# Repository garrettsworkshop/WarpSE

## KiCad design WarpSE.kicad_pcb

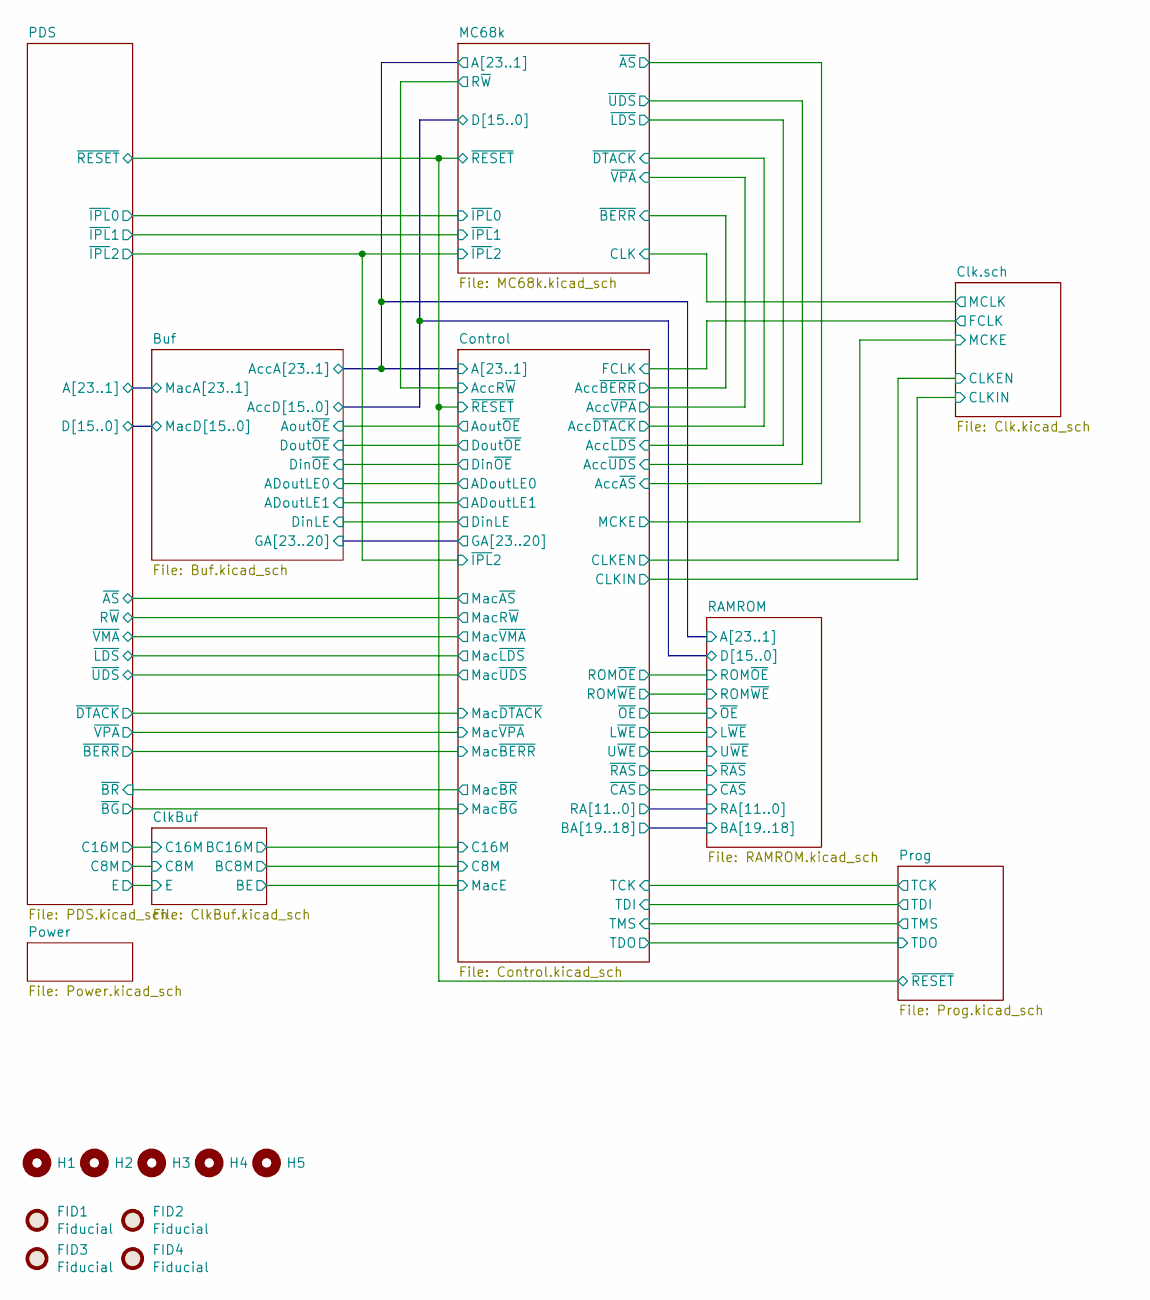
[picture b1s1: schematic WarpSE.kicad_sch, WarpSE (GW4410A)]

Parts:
FID1, FID2, FID3, FID4: Fiducial
H1, H2, H3, H4, H5: PasteHole_1.152mm_NPTH

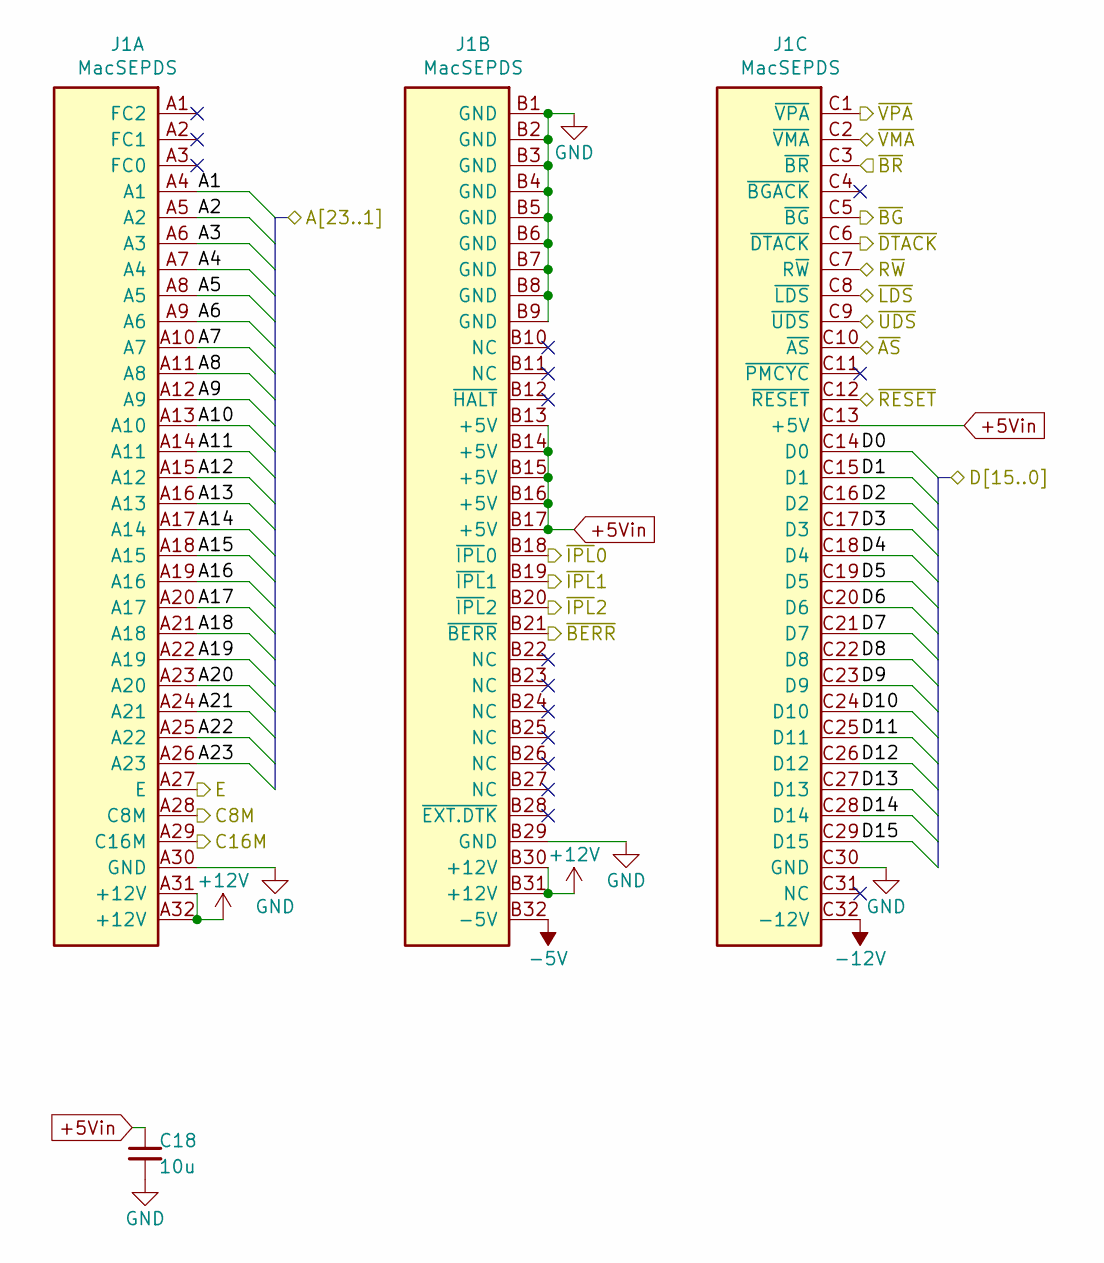
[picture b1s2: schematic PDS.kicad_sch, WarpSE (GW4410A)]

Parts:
C18: 10u; C_0805; LCSC Part C15850
J1: MacSEPDS; DIN41612_R_3x32_Male_Vertical_THT

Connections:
+5Vin: C18.1, J1.B13 (+5V), J1.B14 (+5V), J1.B15 (+5V), J1.B16 (+5V), J1.B17 (+5V), J1.C13 (+5V); also elsewhere on the board
+12V: J1.A31 (+12V), J1.A32 (+12V), J1.B30 (+12V), J1.B31 (+12V)
-5V: J1.B32 (-5V)
-12V: J1.C32 (-12V)
/Buf/MacA1: J1.A4 (A1); also elsewhere on the board
/Buf/MacA2: J1.A5 (A2); also elsewhere on the board
/Buf/MacA3: J1.A6 (A3); also elsewhere on the board
/Buf/MacA4: J1.A7 (A4); also elsewhere on the board
/Buf/MacA5: J1.A8 (A5); also elsewhere on the board
/Buf/MacA6: J1.A9 (A6); also elsewhere on the board
/Buf/MacA7: J1.A10 (A7); also elsewhere on the board
/Buf/MacA8: J1.A11 (A8); also elsewhere on the board
/Buf/MacA9: J1.A12 (A9); also elsewhere on the board
/Buf/MacA10: J1.A13 (A10); also elsewhere on the board
/Buf/MacA11: J1.A14 (A11); also elsewhere on the board
/Buf/MacA12: J1.A15 (A12); also elsewhere on the board
/Buf/MacA13: J1.A16 (A13); also elsewhere on the board
/Buf/MacA14: J1.A17 (A14); also elsewhere on the board
/Buf/MacA15: J1.A18 (A15); also elsewhere on the board
/Buf/MacA16: J1.A19 (A16); also elsewhere on the board
/Buf/MacA17: J1.A20 (A17); also elsewhere on the board
/Buf/MacA18: J1.A21 (A18); also elsewhere on the board
/Buf/MacA19: J1.A22 (A19); also elsewhere on the board
/Buf/MacA20: J1.A23 (A20); also elsewhere on the board
/Buf/MacA21: J1.A24 (A21); also elsewhere on the board
/Buf/MacA22: J1.A25 (A22); also elsewhere on the board
/Buf/MacA23: J1.A26 (A23); also elsewhere on the board
/Buf/MacD0: J1.C14 (D0); also elsewhere on the board
/Buf/MacD1: J1.C15 (D1); also elsewhere on the board
/Buf/MacD2: J1.C16 (D2); also elsewhere on the board
/Buf/MacD3: J1.C17 (D3); also elsewhere on the board
/Buf/MacD4: J1.C18 (D4); also elsewhere on the board
/Buf/MacD5: J1.C19 (D5); also elsewhere on the board
/Buf/MacD6: J1.C20 (D6); also elsewhere on the board
/Buf/MacD7: J1.C21 (D7); also elsewhere on the board
/Buf/MacD8: J1.C22 (D8); also elsewhere on the board
/Buf/MacD9: J1.C23 (D9); also elsewhere on the board
/Buf/MacD10: J1.C24 (D10); also elsewhere on the board
/Buf/MacD11: J1.C25 (D11); also elsewhere on the board
/Buf/MacD12: J1.C26 (D12); also elsewhere on the board
/Buf/MacD13: J1.C27 (D13); also elsewhere on the board
/Buf/MacD14: J1.C28 (D14); also elsewhere on the board
/Buf/MacD15: J1.C29 (D15); also elsewhere on the board
/ClkBuf/C8M: J1.A28 (C8M); also elsewhere on the board
/ClkBuf/C16M: J1.A29 (C16M); also elsewhere on the board
/ClkBuf/E: J1.A27 (E); also elsewhere on the board
/Control/MacR~W: J1.C7 (R~W); also elsewhere on the board
/Control/Mac~AS: J1.C10 (~AS); also elsewhere on the board
/Control/Mac~BERR: J1.B21 (~BERR); also elsewhere on the board
/Control/Mac~BR: J1.C3 (~BR); also elsewhere on the board
/Control/Mac~DTACK: J1.C6 (~DTACK); also elsewhere on the board
/Control/Mac~LDS: J1.C8 (~LDS); also elsewhere on the board
/Control/Mac~UDS: J1.C9 (~UDS); also elsewhere on the board
/Control/Mac~VMA: J1.C2 (~VMA); also elsewhere on the board
/Control/Mac~VPA: J1.C1 (~VPA); also elsewhere on the board
/Control/~IPL2: J1.B20 (~IPL2); also elsewhere on the board
/Control/~RESET: J1.C12 (~RESET); also elsewhere on the board
/MC68k/~IPL0: J1.B18 (~IPL0); also elsewhere on the board
/MC68k/~IPL1: J1.B19 (~IPL1); also elsewhere on the board
/PDS/~BG: J1.C5 (~BG)
GND: C18.2, J1.A30 (GND), J1.B1 (GND), J1.B2 (GND), J1.B3 (GND), J1.B4 (GND), J1.B5 (GND), J1.B6 (GND), J1.B7 (GND), J1.B8 (GND), J1.B9 (GND), J1.B29 (GND), J1.C30 (GND); also elsewhere on the board

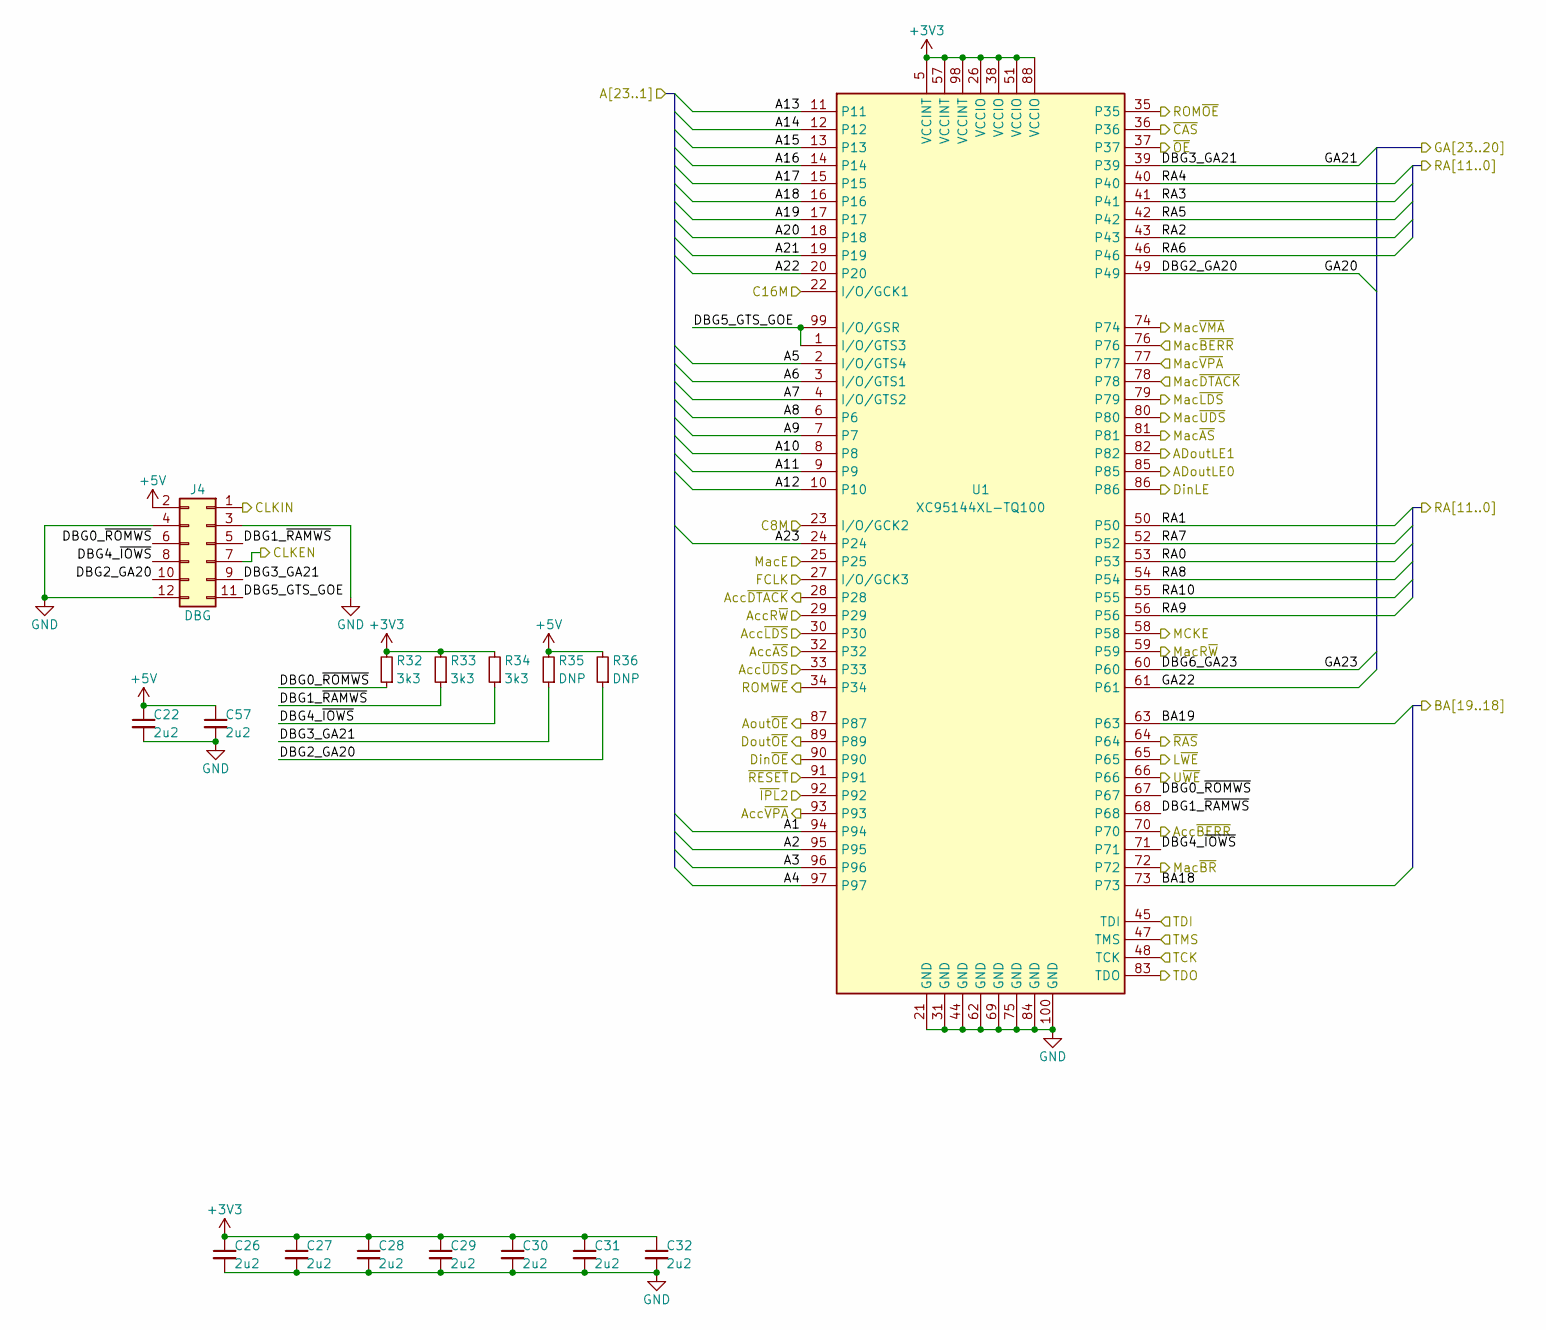
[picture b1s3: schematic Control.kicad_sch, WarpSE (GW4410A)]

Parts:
C22, C26, C27, C28, C29, C30, C31, C32, C57: 2u2; C_0603; LCSC Part C23630
J4: DBG; PinSocket_2x06_P2.00mm_Vertical
R32, R33, R34: 3k3; R_0603; LCSC Part C21190
R35, R36: DNP; R_0603
U1: XC95144XL-TQ100; TQFP-100_14x14mm_P0.5mm; LCSC Part C45126

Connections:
+3V3: C26.1, C27.1, C28.1, C29.1, C30.1, C31.1, C32.1, R32.2, R33.2, R34.2, U1.5 (VCCINT), U1.26 (VCCIO), U1.38 (VCCIO), U1.51 (VCCIO), U1.57 (VCCINT), U1.88 (VCCIO), U1.98 (VCCINT); also elsewhere on the board
+5V: C22.1, C57.1, J4.2, R35.2, R36.2; also elsewhere on the board
/Buf/ADoutLE0: U1.85; also elsewhere on the board
/Buf/ADoutLE1: U1.82; also elsewhere on the board
/Buf/AccA1: U1.94; also elsewhere on the board
/Buf/AccA2: U1.95; also elsewhere on the board
/Buf/AccA3: U1.96; also elsewhere on the board
/Buf/AccA4: U1.97; also elsewhere on the board
/Buf/AccA5: U1.2 (I/O/GTS4); also elsewhere on the board
/Buf/AccA6: U1.3 (I/O/GTS1); also elsewhere on the board
/Buf/AccA7: U1.4 (I/O/GTS2); also elsewhere on the board
/Buf/AccA8: U1.6; also elsewhere on the board
/Buf/AccA9: U1.7; also elsewhere on the board
/Buf/AccA10: U1.8; also elsewhere on the board
/Buf/AccA11: U1.9; also elsewhere on the board
/Buf/AccA12: U1.10; also elsewhere on the board
/Buf/AccA13: U1.11; also elsewhere on the board
/Buf/AccA14: U1.12; also elsewhere on the board
/Buf/AccA15: U1.13; also elsewhere on the board
/Buf/AccA16: U1.14; also elsewhere on the board
/Buf/AccA17: U1.15; also elsewhere on the board
/Buf/AccA18: U1.16; also elsewhere on the board
/Buf/AccA19: U1.17; also elsewhere on the board
/Buf/AccA20: U1.18; also elsewhere on the board
/Buf/AccA21: U1.19; also elsewhere on the board
/Buf/AccA22: U1.20; also elsewhere on the board
/Buf/AccA23: U1.24; also elsewhere on the board
/Buf/Aout~OE: U1.87; also elsewhere on the board
/Buf/DinLE: U1.86; also elsewhere on the board
/Buf/Din~OE: U1.90; also elsewhere on the board
/Buf/Dout~OE: U1.89; also elsewhere on the board
/Buf/GA20: J4.10, R36.1, U1.49; also elsewhere on the board
/Buf/GA21: J4.9, R35.1, U1.39; also elsewhere on the board
/Buf/GA22: U1.61; also elsewhere on the board
/Buf/GA23: U1.60; also elsewhere on the board
/Clk.sch/CLKEN: J4.7; also elsewhere on the board
/Clk.sch/CLKIN: J4.1; also elsewhere on the board
/Clk.sch/FCLK: U1.27 (I/O/GCK3); also elsewhere on the board
/Clk.sch/MCKE: U1.58; also elsewhere on the board
/ClkBuf/BC8M: U1.23 (I/O/GCK2); also elsewhere on the board
/ClkBuf/BC16M: U1.22 (I/O/GCK1); also elsewhere on the board
/ClkBuf/BE: U1.25; also elsewhere on the board
/Control/AccR~W: U1.29; also elsewhere on the board
/Control/Acc~AS: U1.32; also elsewhere on the board
/Control/Acc~BERR: U1.70; also elsewhere on the board
/Control/Acc~DTACK: U1.28; also elsewhere on the board
/Control/Acc~LDS: U1.30; also elsewhere on the board
/Control/Acc~UDS: U1.33; also elsewhere on the board
/Control/Acc~VPA: U1.93; also elsewhere on the board
/Control/BA18: U1.73; also elsewhere on the board
/Control/BA19: U1.63; also elsewhere on the board
/Control/DBG0_~ROMWS: J4.6, R32.1, U1.67
/Control/DBG1_~RAMWS: J4.5, R33.1, U1.68
/Control/DBG4_~IOWS: J4.8, R34.1, U1.71
/Control/DBG5_GTS_GOE: J4.11, U1.1 (I/O/GTS3), U1.99 (I/O/GSR)
/Control/L~WE: U1.65; also elsewhere on the board
/Control/MacR~W: U1.59; also elsewhere on the board
/Control/Mac~AS: U1.81; also elsewhere on the board
/Control/Mac~BERR: U1.76; also elsewhere on the board
/Control/Mac~BR: U1.72; also elsewhere on the board
/Control/Mac~DTACK: U1.78; also elsewhere on the board
/Control/Mac~LDS: U1.79; also elsewhere on the board
/Control/Mac~UDS: U1.80; also elsewhere on the board
/Control/Mac~VMA: U1.74; also elsewhere on the board
/Control/Mac~VPA: U1.77; also elsewhere on the board
/Control/RA0: U1.53; also elsewhere on the board
/Control/RA1: U1.50; also elsewhere on the board
/Control/RA2: U1.43; also elsewhere on the board
/Control/RA3: U1.41; also elsewhere on the board
/Control/RA4: U1.40; also elsewhere on the board
/Control/RA5: U1.42; also elsewhere on the board
/Control/RA6: U1.46; also elsewhere on the board
/Control/RA7: U1.52; also elsewhere on the board
/Control/RA8: U1.54; also elsewhere on the board
/Control/RA9: U1.56; also elsewhere on the board
/Control/RA10: U1.55; also elsewhere on the board
/Control/ROM~OE: U1.35; also elsewhere on the board
/Control/ROM~WE: U1.34; also elsewhere on the board
/Control/TCK: U1.48 (TCK); also elsewhere on the board
/Control/TDI: U1.45 (TDI); also elsewhere on the board
/Control/TDO: U1.83 (TDO); also elsewhere on the board
/Control/TMS: U1.47 (TMS); also elsewhere on the board
/Control/U~WE: U1.66; also elsewhere on the board
/Control/~CAS: U1.36; also elsewhere on the board
/Control/~IPL2: U1.92; also elsewhere on the board
/Control/~OE: U1.37; also elsewhere on the board
/Control/~RAS: U1.64; also elsewhere on the board
/Control/~RESET: U1.91; also elsewhere on the board
GND: C22.2, C26.2, C27.2, C28.2, C29.2, C30.2, C31.2, C32.2, C57.2, J4.3, J4.4, J4.12, U1.21 (GND), U1.31 (GND), U1.44 (GND), U1.62 (GND), U1.69 (GND), U1.75 (GND), U1.84 (GND), U1.100 (GND); also elsewhere on the board

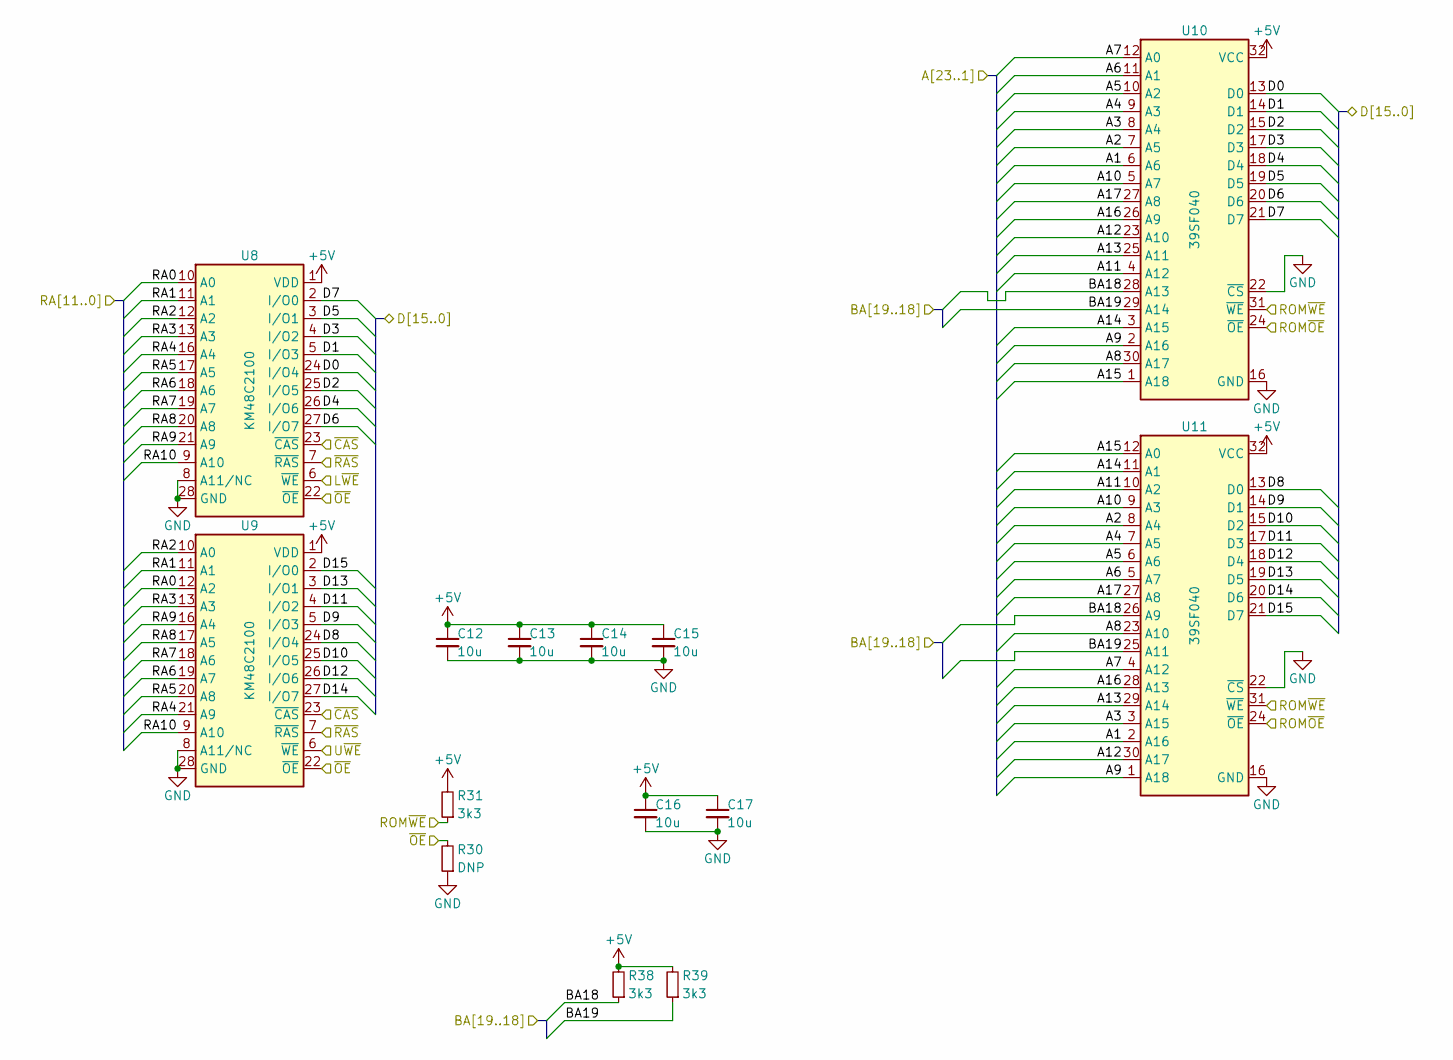
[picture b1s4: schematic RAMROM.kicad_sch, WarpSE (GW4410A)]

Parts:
C12, C13, C14, C15, C16, C17: 10u; C_0805; LCSC Part C15850
R30: DNP; R_0603
R31, R38, R39: 3k3; R_0603; LCSC Part C21190
U8, U9: KM48C2100; SOJ-28_300mil
U10, U11: 39SF040; PLCC-32; LCSC Part C645935

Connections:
+5V: C12.1, C13.1, C14.1, C15.1, C16.1, C17.1, R31.2, R38.2, R39.2, U8.1 (VDD), U8.14 (VDD), U9.1 (VDD), U9.14 (VDD), U10.32 (VCC), U11.32 (VCC); also elsewhere on the board
/Buf/AccA1: U10.6 (A6), U11.2 (A16); also elsewhere on the board
/Buf/AccA2: U10.7 (A5), U11.8 (A4); also elsewhere on the board
/Buf/AccA3: U10.8 (A4), U11.3 (A15); also elsewhere on the board
/Buf/AccA4: U10.9 (A3), U11.7 (A5); also elsewhere on the board
/Buf/AccA5: U10.10 (A2), U11.6 (A6); also elsewhere on the board
/Buf/AccA6: U10.11 (A1), U11.5 (A7); also elsewhere on the board
/Buf/AccA7: U10.12 (A0), U11.4 (A12); also elsewhere on the board
/Buf/AccA8: U10.30 (A17), U11.23 (A10); also elsewhere on the board
/Buf/AccA9: U10.2 (A16), U11.1 (A18); also elsewhere on the board
/Buf/AccA10: U10.5 (A7), U11.9 (A3); also elsewhere on the board
/Buf/AccA11: U10.4 (A12), U11.10 (A2); also elsewhere on the board
/Buf/AccA12: U10.23 (A10), U11.30 (A17); also elsewhere on the board
/Buf/AccA13: U10.25 (A11), U11.29 (A14); also elsewhere on the board
/Buf/AccA14: U10.3 (A15), U11.11 (A1); also elsewhere on the board
/Buf/AccA15: U10.1 (A18), U11.12 (A0); also elsewhere on the board
/Buf/AccA16: U10.26 (A9), U11.28 (A13); also elsewhere on the board
/Buf/AccA17: U10.27 (A8), U11.27 (A8); also elsewhere on the board
/Buf/AccD0: U8.24 (I/O4), U10.13 (D0); also elsewhere on the board
/Buf/AccD1: U8.5 (I/O3), U10.14 (D1); also elsewhere on the board
/Buf/AccD2: U8.25 (I/O5), U10.15 (D2); also elsewhere on the board
/Buf/AccD3: U8.4 (I/O2), U10.17 (D3); also elsewhere on the board
/Buf/AccD4: U8.26 (I/O6), U10.18 (D4); also elsewhere on the board
/Buf/AccD5: U8.3 (I/O1), U10.19 (D5); also elsewhere on the board
/Buf/AccD6: U8.27 (I/O7), U10.20 (D6); also elsewhere on the board
/Buf/AccD7: U8.2 (I/O0), U10.21 (D7); also elsewhere on the board
/Buf/AccD8: U9.24 (I/O4), U11.13 (D0); also elsewhere on the board
/Buf/AccD9: U9.5 (I/O3), U11.14 (D1); also elsewhere on the board
/Buf/AccD10: U9.25 (I/O5), U11.15 (D2); also elsewhere on the board
/Buf/AccD11: U9.4 (I/O2), U11.17 (D3); also elsewhere on the board
/Buf/AccD12: U9.26 (I/O6), U11.18 (D4); also elsewhere on the board
/Buf/AccD13: U9.3 (I/O1), U11.19 (D5); also elsewhere on the board
/Buf/AccD14: U9.27 (I/O7), U11.20 (D6); also elsewhere on the board
/Buf/AccD15: U9.2 (I/O0), U11.21 (D7); also elsewhere on the board
/Control/BA18: R38.1, U10.28 (A13), U11.26 (A9); also elsewhere on the board
/Control/BA19: R39.1, U10.29 (A14), U11.25 (A11); also elsewhere on the board
/Control/L~WE: U8.6 (~WE); also elsewhere on the board
/Control/RA0: U8.10 (A0), U9.12 (A2); also elsewhere on the board
/Control/RA1: U8.11 (A1), U9.11 (A1); also elsewhere on the board
/Control/RA2: U8.12 (A2), U9.10 (A0); also elsewhere on the board
/Control/RA3: U8.13 (A3), U9.13 (A3); also elsewhere on the board
/Control/RA4: U8.16 (A4), U9.21 (A9); also elsewhere on the board
/Control/RA5: U8.17 (A5), U9.20 (A8); also elsewhere on the board
/Control/RA6: U8.18 (A6), U9.19 (A7); also elsewhere on the board
/Control/RA7: U8.19 (A7), U9.18 (A6); also elsewhere on the board
/Control/RA8: U8.20 (A8), U9.17 (A5); also elsewhere on the board
/Control/RA9: U8.21 (A9), U9.16 (A4); also elsewhere on the board
/Control/RA10: U8.9 (A10), U9.9 (A10); also elsewhere on the board
/Control/ROM~OE: U10.24 (~OE), U11.24 (~OE); also elsewhere on the board
/Control/ROM~WE: R31.1, U10.31 (~WE), U11.31 (~WE); also elsewhere on the board
/Control/U~WE: U9.6 (~WE); also elsewhere on the board
/Control/~CAS: U8.23 (~CAS), U9.23 (~CAS); also elsewhere on the board
/Control/~OE: R30.2, U8.22 (~OE), U9.22 (~OE); also elsewhere on the board
/Control/~RAS: U8.7 (~RAS), U9.7 (~RAS); also elsewhere on the board
GND: C12.2, C13.2, C14.2, C15.2, C16.2, C17.2, R30.1, U8.8 (A11/NC), U8.15 (GND), U8.28 (GND), U9.8 (A11/NC), U9.15 (GND), U9.28 (GND), U10.16 (GND), U10.22 (~CS), U11.16 (GND), U11.22 (~CS); also elsewhere on the board

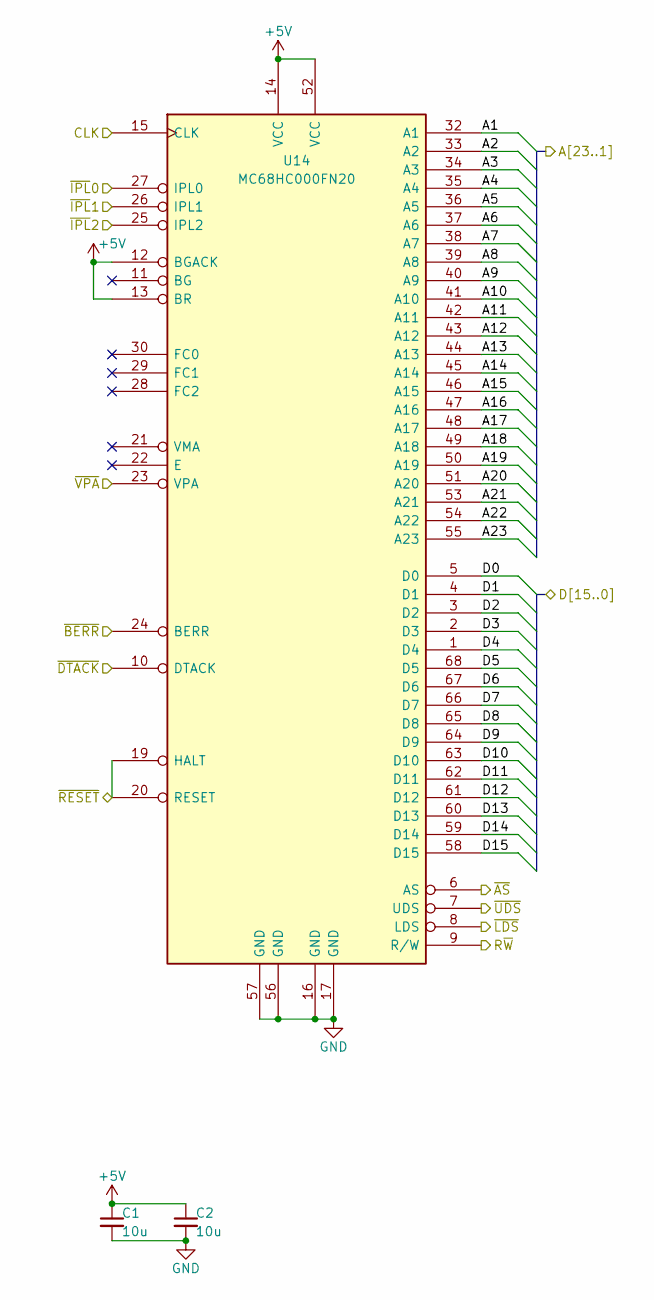
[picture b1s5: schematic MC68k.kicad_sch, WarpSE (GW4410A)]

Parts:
C1, C2: 10u; C_0805; LCSC Part C15850
U14: MC68HC000FN20; PLCC-68

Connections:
+5V: C1.1, C2.1, U14.12 (BGACK), U14.13 (BR), U14.14 (VCC), U14.52 (VCC); also elsewhere on the board
/Buf/AccA1: U14.32 (A1); also elsewhere on the board
/Buf/AccA2: U14.33 (A2); also elsewhere on the board
/Buf/AccA3: U14.34 (A3); also elsewhere on the board
/Buf/AccA4: U14.35 (A4); also elsewhere on the board
/Buf/AccA5: U14.36 (A5); also elsewhere on the board
/Buf/AccA6: U14.37 (A6); also elsewhere on the board
/Buf/AccA7: U14.38 (A7); also elsewhere on the board
/Buf/AccA8: U14.39 (A8); also elsewhere on the board
/Buf/AccA9: U14.40 (A9); also elsewhere on the board
/Buf/AccA10: U14.41 (A10); also elsewhere on the board
/Buf/AccA11: U14.42 (A11); also elsewhere on the board
/Buf/AccA12: U14.43 (A12); also elsewhere on the board
/Buf/AccA13: U14.44 (A13); also elsewhere on the board
/Buf/AccA14: U14.45 (A14); also elsewhere on the board
/Buf/AccA15: U14.46 (A15); also elsewhere on the board
/Buf/AccA16: U14.47 (A16); also elsewhere on the board
/Buf/AccA17: U14.48 (A17); also elsewhere on the board
/Buf/AccA18: U14.49 (A18); also elsewhere on the board
/Buf/AccA19: U14.50 (A19); also elsewhere on the board
/Buf/AccA20: U14.51 (A20); also elsewhere on the board
/Buf/AccA21: U14.53 (A21); also elsewhere on the board
/Buf/AccA22: U14.54 (A22); also elsewhere on the board
/Buf/AccA23: U14.55 (A23); also elsewhere on the board
/Buf/AccD0: U14.5 (D0); also elsewhere on the board
/Buf/AccD1: U14.4 (D1); also elsewhere on the board
/Buf/AccD2: U14.3 (D2); also elsewhere on the board
/Buf/AccD3: U14.2 (D3); also elsewhere on the board
/Buf/AccD4: U14.1 (D4); also elsewhere on the board
/Buf/AccD5: U14.68 (D5); also elsewhere on the board
/Buf/AccD6: U14.67 (D6); also elsewhere on the board
/Buf/AccD7: U14.66 (D7); also elsewhere on the board
/Buf/AccD8: U14.65 (D8); also elsewhere on the board
/Buf/AccD9: U14.64 (D9); also elsewhere on the board
/Buf/AccD10: U14.63 (D10); also elsewhere on the board
/Buf/AccD11: U14.62 (D11); also elsewhere on the board
/Buf/AccD12: U14.61 (D12); also elsewhere on the board
/Buf/AccD13: U14.60 (D13); also elsewhere on the board
/Buf/AccD14: U14.59 (D14); also elsewhere on the board
/Buf/AccD15: U14.58 (D15); also elsewhere on the board
/Clk.sch/MCLK: U14.15 (CLK); also elsewhere on the board
/Control/AccR~W: U14.9 (R/W); also elsewhere on the board
/Control/Acc~AS: U14.6 (AS); also elsewhere on the board
/Control/Acc~BERR: U14.24 (BERR); also elsewhere on the board
/Control/Acc~DTACK: U14.10 (DTACK); also elsewhere on the board
/Control/Acc~LDS: U14.8 (LDS); also elsewhere on the board
/Control/Acc~UDS: U14.7 (UDS); also elsewhere on the board
/Control/Acc~VPA: U14.23 (VPA); also elsewhere on the board
/Control/~IPL2: U14.25 (IPL2); also elsewhere on the board
/Control/~RESET: U14.19 (HALT), U14.20 (RESET); also elsewhere on the board
/MC68k/~IPL0: U14.27 (IPL0); also elsewhere on the board
/MC68k/~IPL1: U14.26 (IPL1); also elsewhere on the board
GND: C1.2, C2.2, U14.16 (GND), U14.17 (GND), U14.56 (GND), U14.57 (GND); also elsewhere on the board

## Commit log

2021-10-29 add from other repo
2021-11-01 Fixed doc bug
2021-11-02 Documentation update
2021-11-02 Update SE-030.kicad_pcb
    More via stitching
2022-01-03 Before I remove ESP32
2022-01-27 Moving toward new update system
2022-02-01 Migrate to KiCad 6
2022-02-14 Added RAM/ROM address multiplexing
2022-02-14 Move directories
2022-02-14 Change pins to fix BERR issue
2022-02-16 Update sym-lib-table
2022-03-28 Prototype
2022-03-28 Update FrontIsom
2022-03-29 Better CPLD stuff
2022-04-05 working on SDRAM
2022-04-06 Add power adapter
2022-04-12 More work on power adapter
2022-04-13 Switch to '030
2022-04-13 Update gitignore
2022-04-19 Ignore kicad_prl files
2022-04-19 With new logo
2022-04-19 "Rotation" in top-pos
2022-04-19 Correct orientation for ROM sockets
2022-04-19 Actually fix orientation
2022-04-20 Fix ROM 3dmodel orientation
2022-04-22 Finished power adapter?
2022-05-25 Power adapter as sent to JLC
2022-06-07 As sent to JLC
2022-09-04 New stuff
2022-09-05 idk more
2022-09-11 POR changes
2022-09-14 more
2023-02-12 ROM swap stuff
2023-03-20 Improved a lot of stuff
2023-03-20 Better
2023-03-20 Update RAM.v
    Remove old RAMDIS1 stuff
2023-03-25 Starts up
2023-03-25 Redo CNT timers
2023-03-26 Fix ROM endianness
2023-03-27 Reorganize rom build
2023-03-27 Put back all chip selects.
2023-03-30 Fixing this up some more
2023-03-30 IOBS and ROM overlay fixes
2023-03-31 Improved overlay latching
2023-03-31 Fixed IOBS bugs
2023-03-31 Rename "Once" to "Sent" in IOBS
2023-04-01 Fixed cycle termination signal synchronization in IOBM
2023-04-01 Works well but fast RAM disabled
2023-04-01 Fix RAM?
2023-04-01 Better but RAM still not right... soldering error in prototype?
2023-04-02 RAM addressing fix
2023-04-02 Better addressing
2023-04-07 Much better RAM and FSB controller draft
2023-04-07 Works with new Ready. RAM still untested
2023-04-07 RAM working!!
2023-04-07 Fix IOPWReady timing
2023-04-08 Fix IOBS typo
2023-04-08 Reduce refresh urgent period
2023-04-08 Narrow RAM selection range
2023-04-08 Add sound QoS back
2023-04-08 Treat C20MEN as input now
2023-04-08 CS fixes
2023-04-08 Fix typos in recent commits
2023-04-09 Sound QoS working?
2023-04-10 Fix some comments in CNT module
2023-04-10 Change ready behavior during sound slowdown
2023-04-10 Put back full RAM refresh conditions
2023-04-10 Share IOPWReady with ALE1 in IOBS
2023-04-10 Redo overlay bit to remove ODCSr register
2023-04-10 Revert "Share IOPWReady with ALE1 in IOBS"
    This reverts commit 8fc04a86a8d00bfd37a9f8b767e1a5cadd6638ef.
2023-04-10 Revert "Revert "Share IOPWReady with ALE1 in IOBS""
    This reverts commit 388e381dffbac52b96e6708a5b6d923056fda0cb.
2023-04-10 Revert "Put back full RAM refresh conditions"
    This reverts commit adb25788215384c46a7916dda93912e9f234fa1a.
2023-04-10 Works. IOPWReady eliminated
2023-04-10 Works well again with speculative RAM refresh
2023-04-10 New RAM controller
2023-04-11 Fixed
2023-04-15 Fixed RAM
2023-04-15 Compiled
2023-04-15 More comments in RAM controller
2023-04-17 Try shortening refresh
2023-04-17 Revert "Try shortening refresh"
    This reverts commit 335232eae24c704fa4f86deb3e3dad7e846c77dd.
2023-04-30 Toward final "A"
2023-07-13 Fix some CPLD typos
2023-07-16 Revert "idk"
    This reverts commit 06688d2caf5c826e128d92688927a007f94f5988.
2023-07-16 Revert "Fix some CPLD typos"
    This reverts commit 0a532676a141ee53dff6ecefa9564a2b2a8f2338.
2023-07-16 Revert "idk"
    This reverts commit aa30aa8a559ae1d3e965923a55380a6d00f93ea4.
2023-07-16 Works including credit-based sound slowdown
    works
2023-09-28 Put back old Sound QoS... not debit-based
2023-11-07 final version?
2023-11-07 toward final
2023-11-27 Remove power adapter
2023-11-27 Update to new makefile, etc.
2024-01-27 remove gerbers?
2024-05-04 better PDS muxing
2024-06-11 Moving to QFP144 ECP5
2024-06-11 Update Makefile
2024-09-12 Improve 3V3 routing under XC95144XL
2024-09-22 Add DBG header pinout to ucf constraints file
2024-09-22 Fix bad wiring for CNT module
2024-09-22 Switch DBG to input to save macrocells
2024-09-22 Update RAM module inputs/outputs
2024-09-22 Rename "sound QoS" comments in module declaration/instantiation
2024-09-22 Add reset synchronization to CNT module
2024-09-22 Fix long timer comments -- no longer used for QoS
2024-09-22 IACK now just based on A[23:20] instead of A[23:16]
2024-09-22 USB power
2024-09-22 New slowdown/QoS strategy -- everything goes out to the PDS bus
2024-09-23 Remake project file
2024-09-24 Fix I/O slowdown
2024-09-26 Remake project again
2024-09-29 New more cycle-accurate slowdown
2024-09-29 Add LM66100 instead of MAX40200AUK
2024-09-29 Additional sound QoS
2024-09-29 Revert "Additional sound QoS"
    This reverts commit 3a8f07e71be1645293ea642adaef451a92467c0e.
2024-09-30 Better sound, restore fast SCSI
2024-10-01 simplifying CPLD functions, add IOB RW, slow SCSI back down
2024-10-01 Works with simplified IOBS/IOBM
2024-10-01 Remove MCKE gate and shorten POR
2024-10-03 Board prerelease revision 3 with USB power, A[23:20] remapping
2024-10-03 Back to "old robust"
2024-10-03 Add "new old"
2024-10-03 Redo timers, init, QoS
2024-10-03 PDS bridge refactor
2024-10-03 Fix RAM.v to compile
2024-10-03 Fix WarpSE.v QosEN declaration
2024-10-03 Add PDS R/W to top level entity
2024-10-03 0.6a compiled and works
2024-10-03 Fix bug in CNT.v
2024-10-03 Add CNT area reduction from 0.6e
2024-10-03 0.6b compiled and works
2024-10-03 Improve refresh performance
2024-10-03 0.6c compiled and works
2024-10-03 0.6d compiled and works
2024-10-07 Fix some RAM issues (is RAMEN fix really necessary?)
2024-10-07 Revert to old FSB DTACK/VPA control
2024-10-07 Fix /VMA setup time before E clock
2024-10-07 0.6e compiled and works
2024-10-07 Add slow slew rate constraints for PDS bus outputs
2024-10-07 Remove PDS R/W from top-level entity
2024-10-07 Revert "Revert to old FSB DTACK/VPA control"
    This reverts commit 2912399c2ed93298911e9752427213e736df90e4.
2024-10-07 Rename RAMReady to make it easier to eliminate later
2024-10-07 Fix typos in IOBM
2024-10-07 New IODONE edge detect in IOBS -- no need to limit IODONE pulse width in IOBM
2024-10-07 Eliminate IOBERR
2024-10-07 More /VMA setup time matching MC68k timing
2024-10-07 Register /DTACK at C16M clock edge instead
2024-10-07 Extra 1/2 FCLK IODONE delay
2024-10-07 Slow slew rate on more outputs
2024-10-07 /ROMWE gated with BACTr
2024-10-07 New RAM /OE control so it doesn't bus fight
2024-10-07 Better comments in RAM controller
2024-10-07 0.6f compiled and working
2024-10-08 Remove sound-specific QoS
2024-10-08 Add PDS R/W back
2024-10-08 Formatting changes in RAM.v
2024-10-08 Gate RAM /OE with RAMCS instead of RAMCS0X
2024-10-08 Revised comments in IOBM
2024-10-08 Reformat DoutOE equation in IOBM
2024-10-08 Turn off FSB data output onto PDS bus when PDS bus idle
2024-10-08 PDS R/W output in IOBM latches IORW after assertion
2024-10-08 Fix PDS R/W constraint
2024-10-08 Gate writes to motherboard RAM/ROM into reads.
2024-10-09 Revise comments in RAM.v
2024-10-09 RAM /OE asynchronously reset by /AS rising
2024-10-09 Remove BACTr from ROM /WE equation
2024-10-09 RAM RefDone reset by RefReqIn only. No longer depends on RefUrg too
2024-10-09 Actually assign PDS R/W signal to I/O pin
2024-10-09 0.6g compiled. Should work but untested
2024-10-09 Undo I/O R/W gate for now. Will have to re-add this later for new revision with PDS R/W connected to CPLD.
2024-10-09 Make PDS /BR open-drain
2024-10-09 0.6h compiled and working
2024-10-09 Output ASrf from FSB unit
2024-10-09 Add back 68k clock gated slowdown
2024-10-09 0.6i compiled and working
2024-10-09 Hm actual 0.6i
2024-10-11 Add slowdown settings
2024-10-11 Add settings module power-on reset
2024-10-11 0.7a compiled and working
2024-10-11 0.7a-35us compiled
2024-10-11 0.7a-slow compiled
2024-10-11 0.7a-slow-noclockgate compiled
2024-10-11 0.7a-fastscsi compiled
2024-10-12 0.6a-noclockgate compiled
2024-10-12 0.7a-35us-noclockgate compiled
2024-10-12 0.7a-fast compiled
2024-10-12 0.6a-fastscsi-noclockgate compiled
2024-10-12 0.7a-fastscsi-35us-noclockgate compiled
2024-10-12 0.7a-fastscsi-35us compiled
2024-10-12 0.7a-fastiack compiled
2024-10-12 0.7a-fastiack-35us compiled
2024-10-12 0.7a-fastiack-35us-noclockgate
2024-10-12 0.7a-fastiack-noclockgate compiled
2024-10-12 0.7a-fastiack-fastscsi
2024-10-12 0.7a-fastiack-fastscsi-35us compiled
2024-10-12 0.7a-fastiack-fastscsi-35us-noclockgate compiled
2024-10-12 0.7a-fastiack-fastscsi-noclockgate compiled
2024-10-12 0.7a-fastscc compiled
2024-10-12 0.7a-fastscc-35us compiled
2024-10-12 0.7a-fastscc-35us-noclockgate
2024-10-12 0.7a-fastscc-noclockgate compiled
2024-10-12 0.7a-fastiack-fastscc compiled
2024-10-12 0.7a-fastiack-fastscc-35us compiled
2024-10-12 0.7a-fastiack-fastscc-35us-noclockgate compiled
2024-10-12 0.7a-fastiack-fastscc-noclockgate compiled
2024-10-12 0.7a-fastiack-fastscc-fastscsi compiled
2024-10-12 0.7a-fastiack-fastscc-fastscsi-35us compiled
2024-10-12 0.7a-fastiack-fastscc-fastscsi-35us-noclockgate compiled
2024-10-12 0.7a-fastiack-fastscc-fastscsi-noclockgate compiled
2024-10-12 put 0.7a source, .jed, etc back and recompile
2024-10-13 Change default settings
2024-10-13 Differentiate sound and other I/O QoS selects in CNT
2024-10-13 Make QoS slowdown respect timeout setting
2024-10-13 Clock always gated during sound slowdown but immediately resumes 25 MHz after
2024-10-14 0.7b compiled and working
2024-10-15 0.7c compiled and working
2024-10-15 0.7c-fast compiled and working
2024-10-15 0.7c-slow compiled and working
2024-10-15 Go back to 0.7c
2024-10-16 New QoS with speedup counter
2024-10-16 0.7d compiled and working
2024-10-16 0.7d-slowscc compiled and working
2024-10-16 0.7d-fastscc compiled and works
2024-10-16 Add 0.7d-fastscc and slowscc
2024-10-16 Put back fatsscc
2024-10-17 Add back settings
2024-10-17 Just one setting, whether sound accesses trigger slowdown
2024-10-20 Add OC board
2024-10-20 More PLD toward final version
2024-10-20 Before switching to SiT2001 oscillator
2024-10-22 Remove overclocking board
2024-10-22 Board changes
2024-10-22 Firmware changes for board changes
2024-10-23 Remove old CPLD stuff
2024-10-26 Before remove first clock input buffer
2024-11-05 C8M-based POR supports higher fast clock frequencies
2024-11-05 "Prince of Persia" fix -- more slowdown time after VIA access
2024-11-05 Speed up after SCSI access
2024-11-05 Shorten LTimer period
2024-11-05 Startup sequence rewritten for shorter LTimer period
2024-11-05 0.7e compiled and works
2025-01-10 Final A?
2025-03-30 just a schematic change?
